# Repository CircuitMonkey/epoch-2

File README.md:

# epoch-2
Epoch Vibrator Controller *(Haptic Field Emitter)* 2 - Now with 100% more edge...

## Description
A follow on to [Epoch 1](https://github.com/CircuitMonkey/epoch).  Designed in 2025. Replaced by [Epoch 3](https://github.com/CircuitMonkey/epoch-3) in 2026. Redesigned with [AdaFruit Qualia ESP32](https://www.adafruit.com/product/5800) and a [Amazon 4-inch IPS (GT911 touch)](https://www.amazon.com/dp/B0D9H3HWR3).  Motors driven with [pca9685 PWM controller](https://learn.adafruit.com/adafruit-16-channel-pwm-servo-hat-for-raspberry-pi)/[Amazon PCA9685 Board](https://www.amazon.com/dp/B0D73811V8) and FET outputs in order to drive bigger motors.  Epoch 1 was limited to 120mA maximum motor drive (because of PWM controller choice) and some larger "rumble" motors need 180mA or higher.

## Features
 - [Adafruit Qualia ESP32-S3 RGB666](https://www.adafruit.com/product/5800)
 - [Amazon 4-inch IPS (GT911 touch)](https://www.amazon.com/dp/B0D9H3HWR3)
 - [pca9685 PWM controller](https://learn.adafruit.com/adafruit-16-channel-pwm-servo-hat-for-raspberry-pi)
 - [LiPo Battery - 62mm x 50mm, 2500mAH, Adafruit](https://www.adafruit.com/product/328)
 - TRS 3.5mm type cables (two motors per connector)
 - FET outputs in order to drive bigger motors.
 - Used [Electric Mini Micro Vibration Motor DC 1.5V/3V/6V 1000RPM M20 with Brass Eccentric Rotating Wheel ](https://www.amazon.com/dp/B07X7MKKQH) in attachments.
 - Programmed in CircuitPython.

## Dev Notes
 - Hardware was intended to output all 16 channels as two rows of connectors, but only built one row.
 - IPS type display used most of the ESP32 pins.
 - Circuit Python with the IPS display was excrucatingly slow.
 - Touch response time was very slow with Circuit Python and made on-screen sliders frustrating to use.
 - TRS Audio type connectors were a big improvement over Molex MinifitJr type connectors.
 - This platform performed well for almost a year, before Epoch-3 developed.
 - Experimental air pressure input showed promise but was fussy in setup/use and not worth using long term.
 - PCA9685 PWM driver was much easier to code with over older Epoch-1 PWM driver.
 - FET outputs allowed use of slightly bigger motors with more rumble yet allowed for a lower motor speeds for subtle haptic sensations.
 - Custom molds were 3D printed for attachments where silicone was poured over a TPU flex frame that held the motors.
 - Attachments had LEDs built in to indicate intensity of each motor.
 - This design and motor patterns have changed my life, able to realize two or three hour long usage sessions.
 - I look forward to improving on this design in Epoch 3.

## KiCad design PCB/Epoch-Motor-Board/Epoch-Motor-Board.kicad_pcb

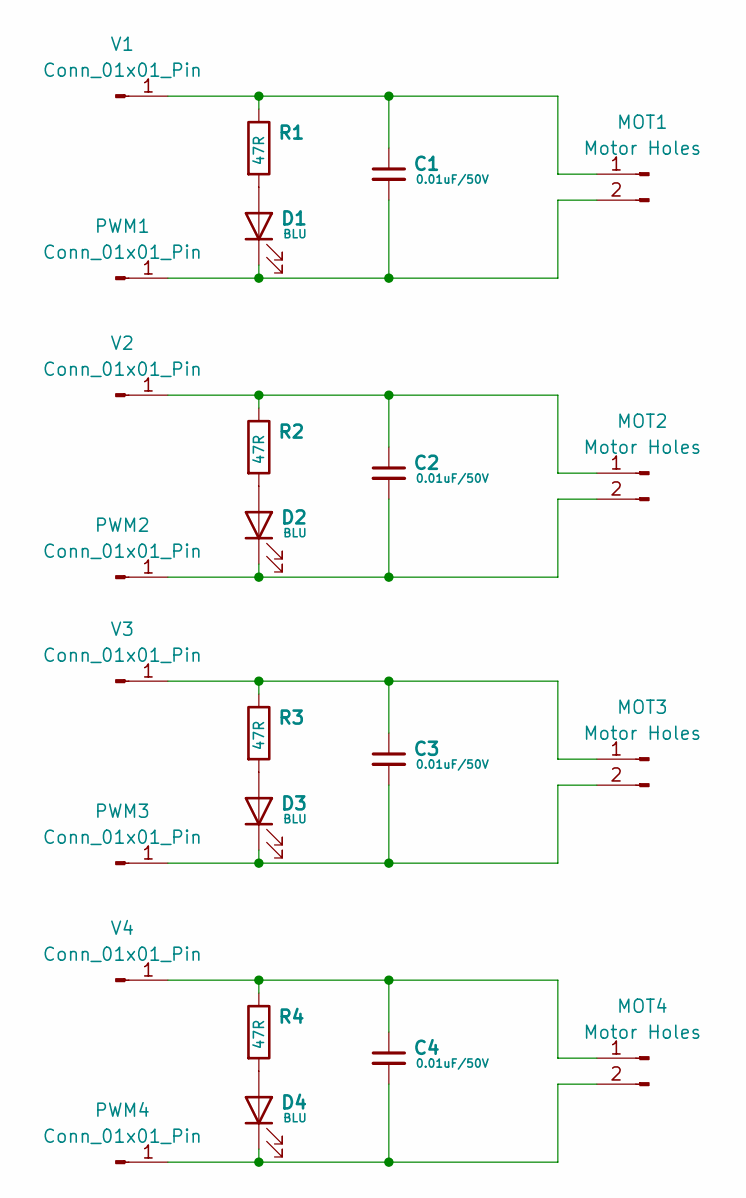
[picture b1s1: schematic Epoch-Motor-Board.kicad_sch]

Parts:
C1, C2, C3, C4: 0.01uF/50V; C_0603_1608Metric
D1, D2, D3, D4: BLU; LED_0603_1608Metric
MOT1, MOT2, MOT3, MOT4: Motor Holes; Motor-PCB
PWM1, PWM2, PWM3, PWM4: Conn_01x01_Pin; TestPoint_Pad_D2.0mm
R1, R2, R3, R4: 47R; R_0603_1608Metric
V1, V2, V3, V4: Conn_01x01_Pin; TestPoint_Pad_2.0x2.0mm

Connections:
unnamed: D1.2 (A), R1.2
unnamed: C1.2, D1.1 (K), MOT1.2, PWM1.1
unnamed: D2.2 (A), R2.2
unnamed: C2.2, D2.1 (K), MOT2.2, PWM2.1
unnamed: D3.2 (A), R3.2
unnamed: C3.2, D3.1 (K), MOT3.2, PWM3.1
unnamed: D4.2 (A), R4.2
unnamed: C4.2, D4.1 (K), MOT4.2, PWM4.1
unnamed: C1.1, MOT1.1, R1.1, V1.1
unnamed: C2.1, MOT2.1, R2.1, V2.1
unnamed: C3.1, MOT3.1, R3.1, V3.1
unnamed: C4.1, MOT4.1, R4.1, V4.1

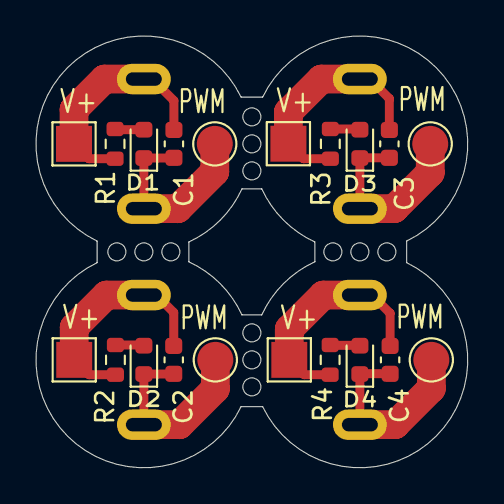
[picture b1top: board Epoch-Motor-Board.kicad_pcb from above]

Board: 2 copper layers, 24.0 x 24.0 mm, 24 parts (0 on the bottom side), 12 nets.

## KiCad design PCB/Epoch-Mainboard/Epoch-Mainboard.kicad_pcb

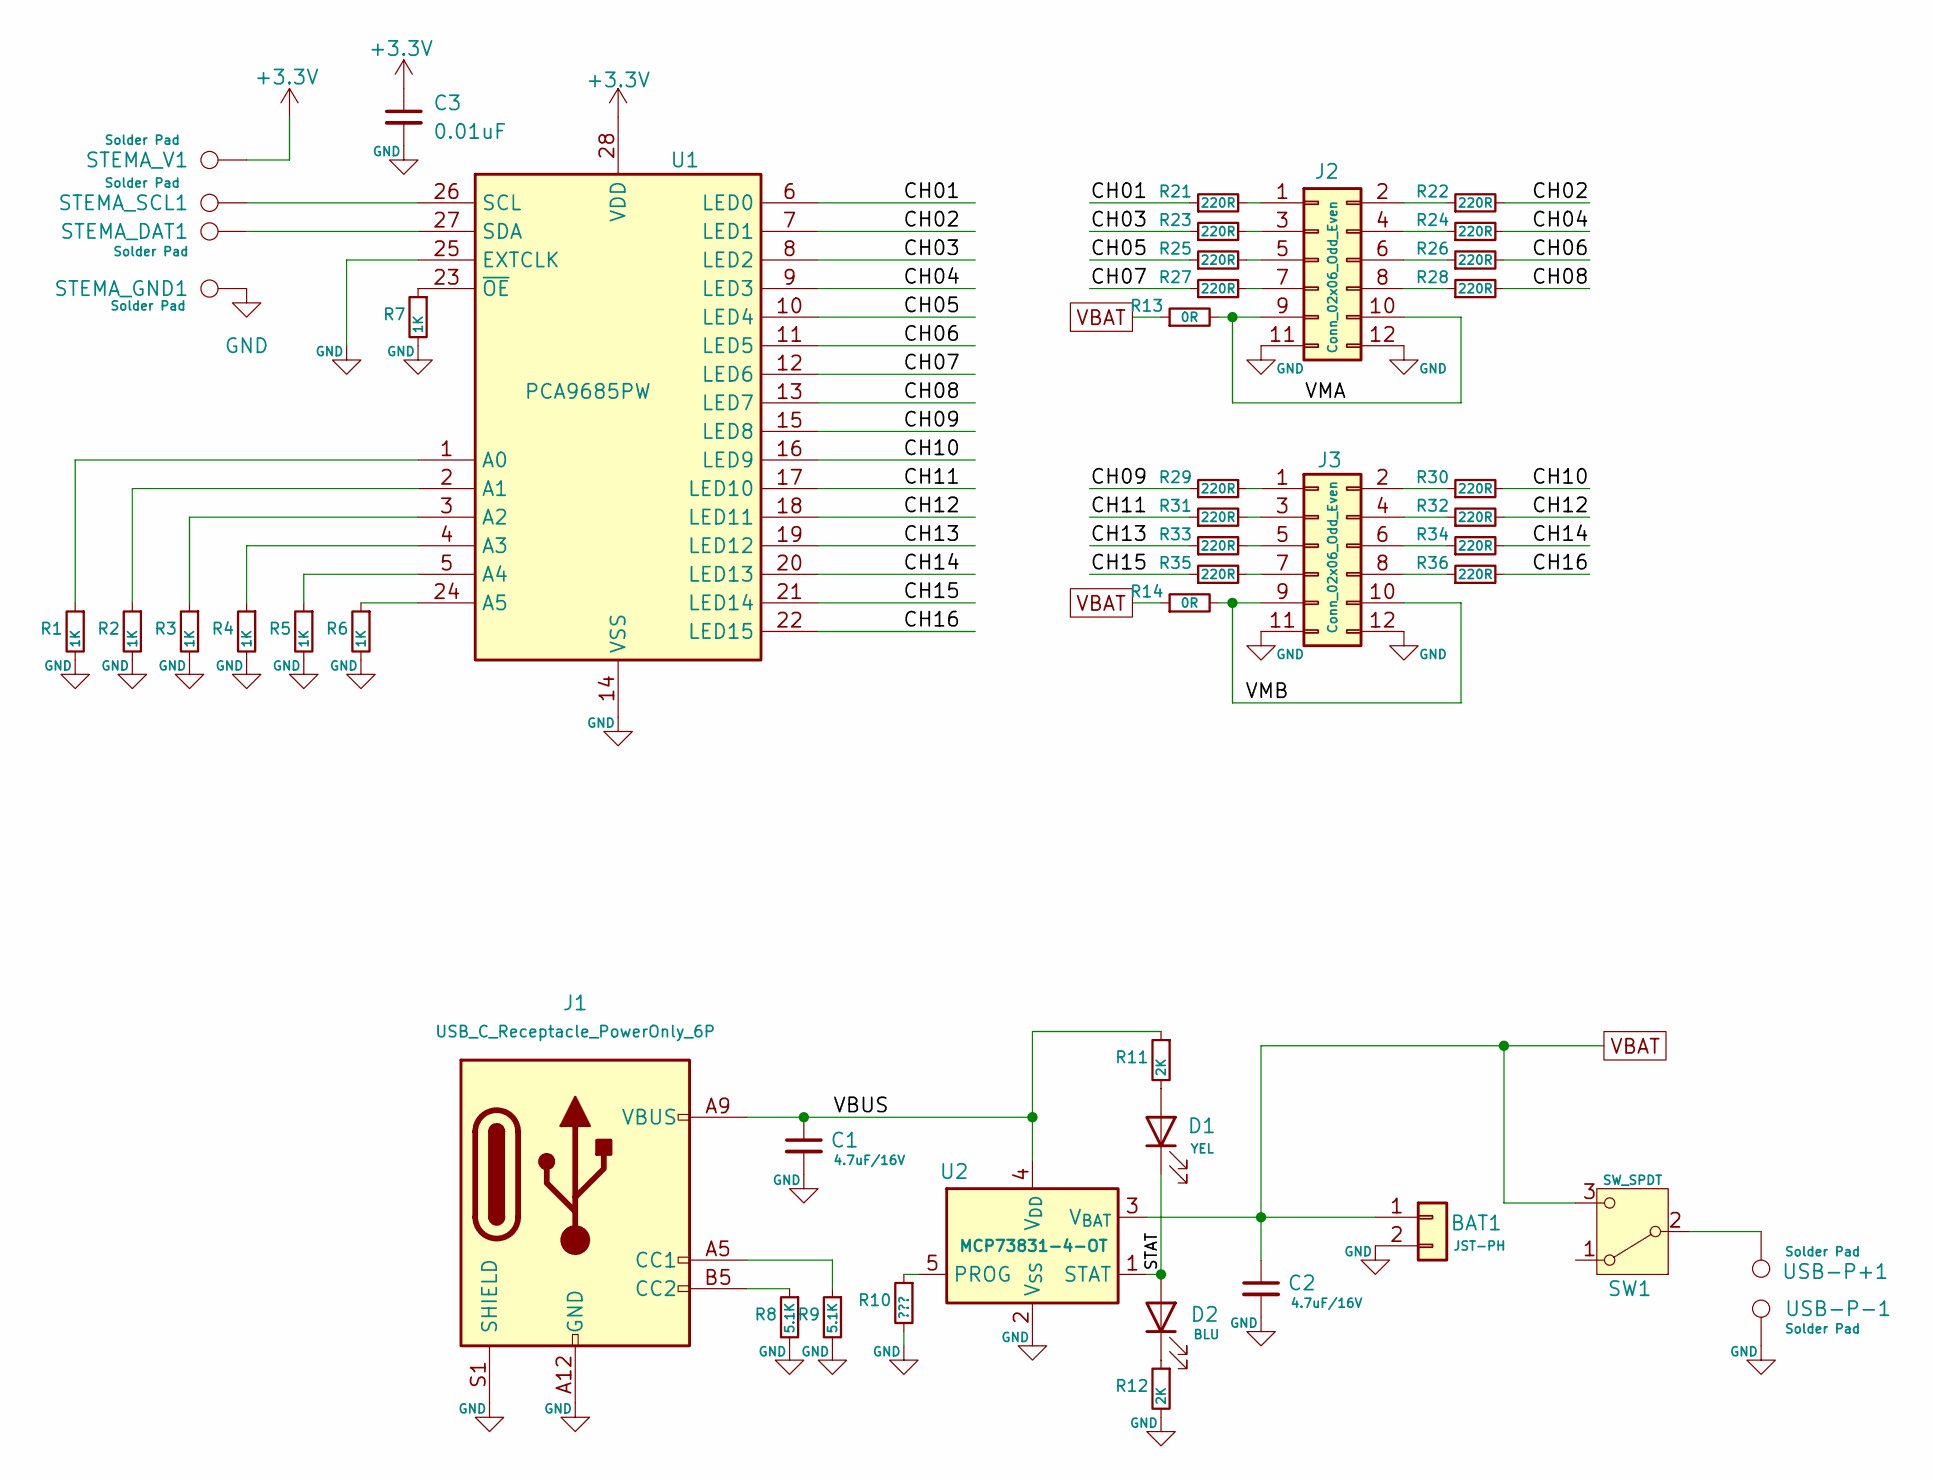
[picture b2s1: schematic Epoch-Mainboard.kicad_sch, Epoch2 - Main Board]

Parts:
BAT1: JST-PH; JST_PH_S2B-PH-K_1x02_P2.00mm_Horizontal
C1, C2: 4.7uF/16V; C_0603_1608Metric
C3: 0.01uF; C_0603_1608Metric
D1: YEL; LED_0603_1608Metric
D2: BLU; LED_0603_1608Metric
J1: USB_C_Receptacle_PowerOnly_6P; USB_C_Receptacle_HRO_TYPE-C-31-M-17
J2, J3: Conn_02x06_Odd_Even; PinHeader_2x06_P2.54mm_Vertical
R1, R2, R3, R4, R5, R6, R7: 1K; R_0603_1608Metric
R8, R9: 5.1K; R_0603_1608Metric
R10: ???; R_0603_1608Metric
R11, R12: 2K; R_0603_1608Metric
R13, R14: 0R; R_1206_3216Metric
R21, R22, R23, R24, R25, R26, R27, R28, R29, R30, R31, R32, R33, R34, R35, R36: 220R; R_0603_1608Metric
STEMA_DAT1: Solder Pad; TestPoint_Pad_D2.0mm
STEMA_GND1: Solder Pad; TestPoint_Pad_D2.0mm
STEMA_SCL1: Solder Pad; TestPoint_Pad_D2.0mm
STEMA_V1: Solder Pad; TestPoint_Pad_D2.0mm
SW1: SW_SPDT; SW_Slide_SPDT_Angled_CK_OS102011MA1Q
U1: PCA9685PW; TSSOP-28_4.4x9.7mm_P0.65mm
U2: MCP73831-4-OT; SOT-23-5
USB-P+1: Solder Pad; TestPoint_Pad_D2.0mm
USB-P-1: Solder Pad; TestPoint_Pad_D2.0mm

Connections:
+3.3V: C3.1, STEMA_V1.1, U1.28 (VDD)
/CH01: R21.1, U1.6 (LED0)
/CH02: R22.2, U1.7 (LED1)
/CH03: R23.1, U1.8 (LED2)
/CH04: R24.2, U1.9 (LED3)
/CH05: R25.1, U1.10 (LED4)
/CH06: R26.2, U1.11 (LED5)
/CH07: R27.1, U1.12 (LED6)
/CH08: R28.2, U1.13 (LED7)
/CH09: R29.1, U1.15 (LED8)
/CH10: R30.2, U1.16 (LED9)
/CH11: R31.1, U1.17 (LED10)
/CH12: R32.2, U1.18 (LED11)
/CH13: R33.1, U1.19 (LED12)
/CH14: R34.2, U1.20 (LED13)
/CH15: R35.1, U1.21 (LED14)
/CH16: R36.2, U1.22 (LED15)
/STAT: D1.1 (K), D2.2 (A), U2.1 (STAT)
/VBUS: C1.1, J1.A9 (VBUS), J1.B9 (VBUS), R11.1, U2.4 (V_{DD})
/VMA: J2.9, J2.10, R13.2
/VMB: J3.9, J3.10, R14.2
GND: BAT1.2, C1.2, C2.2, C3.2, J1.A12 (GND), J1.B12 (GND), J1.S1 (SHIELD), J2.11, J2.12, J3.11, J3.12, R1.2, R2.2, R3.2, R4.2, R5.2, R6.2, R7.2, R8.2, R9.2, R10.2, R12.2, STEMA_GND1.1, U1.14 (VSS), U1.25 (EXTCLK), U2.2 (V_{SS}), USB-P-1.1
unnamed: D1.2 (A), R11.2
unnamed: D2.1 (K), R12.1
unnamed: J1.A5 (CC1), R9.1
unnamed: J1.B5 (CC2), R8.1
unnamed: J2.1, R21.2
unnamed: J2.2, R22.1
unnamed: J2.3, R23.2
unnamed: J2.4, R24.1
unnamed: J2.5, R25.2
unnamed: J2.6, R26.1
unnamed: J2.7, R27.2
unnamed: J2.8, R28.1
unnamed: J3.1, R29.2
unnamed: J3.2, R30.1
unnamed: J3.3, R31.2
unnamed: J3.4, R32.1
unnamed: J3.5, R33.2
unnamed: J3.6, R34.1
unnamed: J3.7, R35.2
unnamed: J3.8, R36.1
unnamed: SW1.2 (B), USB-P+1.1
unnamed: R1.1, U1.1 (A0)
unnamed: R2.1, U1.2 (A1)
unnamed: R3.1, U1.3 (A2)
unnamed: R4.1, U1.4 (A3)
unnamed: R5.1, U1.5 (A4)
unnamed: R6.1, U1.24 (A5)
unnamed: STEMA_SCL1.1, U1.26 (SCL)
unnamed: STEMA_DAT1.1, U1.27 (SDA)
unnamed: R7.1, U1.23 (~OE)
unnamed: R10.1, U2.5 (PROG)
VBAT: BAT1.1, C2.1, R13.1, R14.1, SW1.3 (C), U2.3 (V_{BAT})

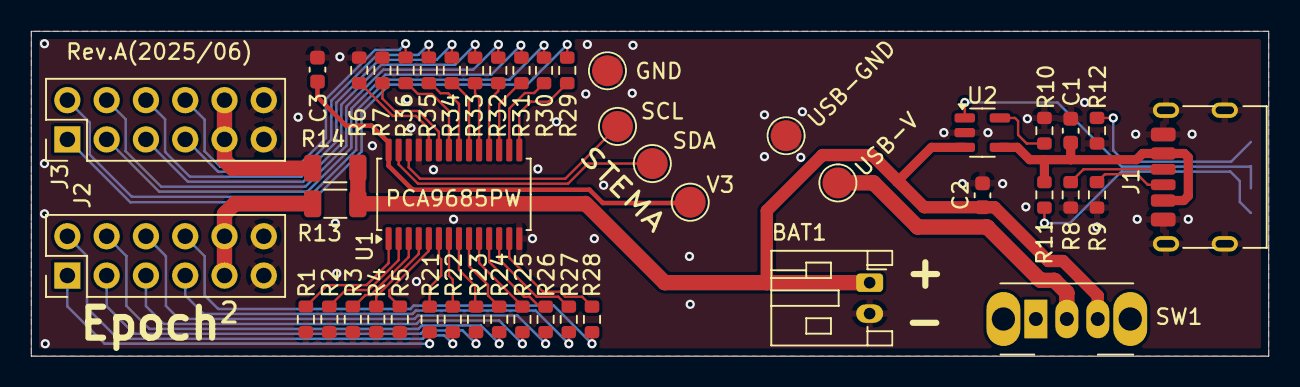
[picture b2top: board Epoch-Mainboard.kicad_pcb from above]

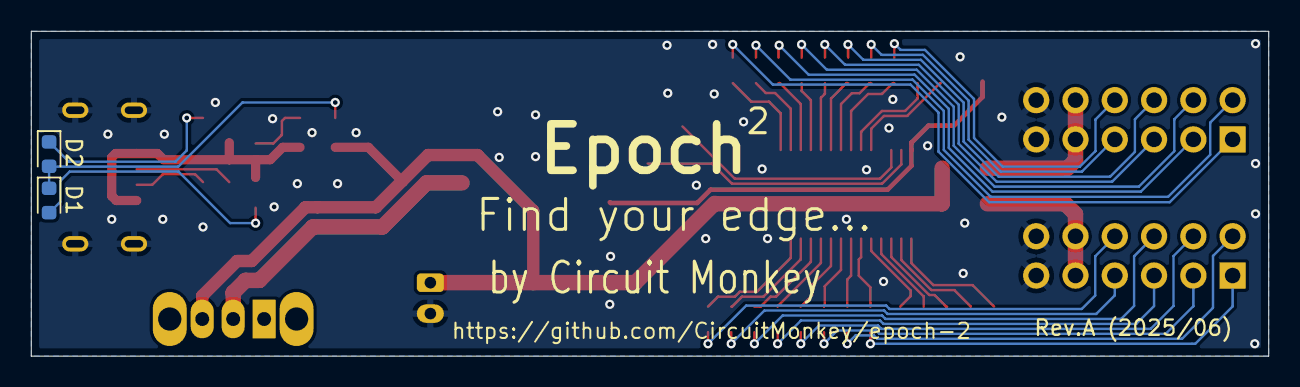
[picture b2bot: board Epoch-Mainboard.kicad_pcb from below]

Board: 2 copper layers, 80.0 x 21.0 mm, 48 parts (2 on the bottom side), 54 nets.

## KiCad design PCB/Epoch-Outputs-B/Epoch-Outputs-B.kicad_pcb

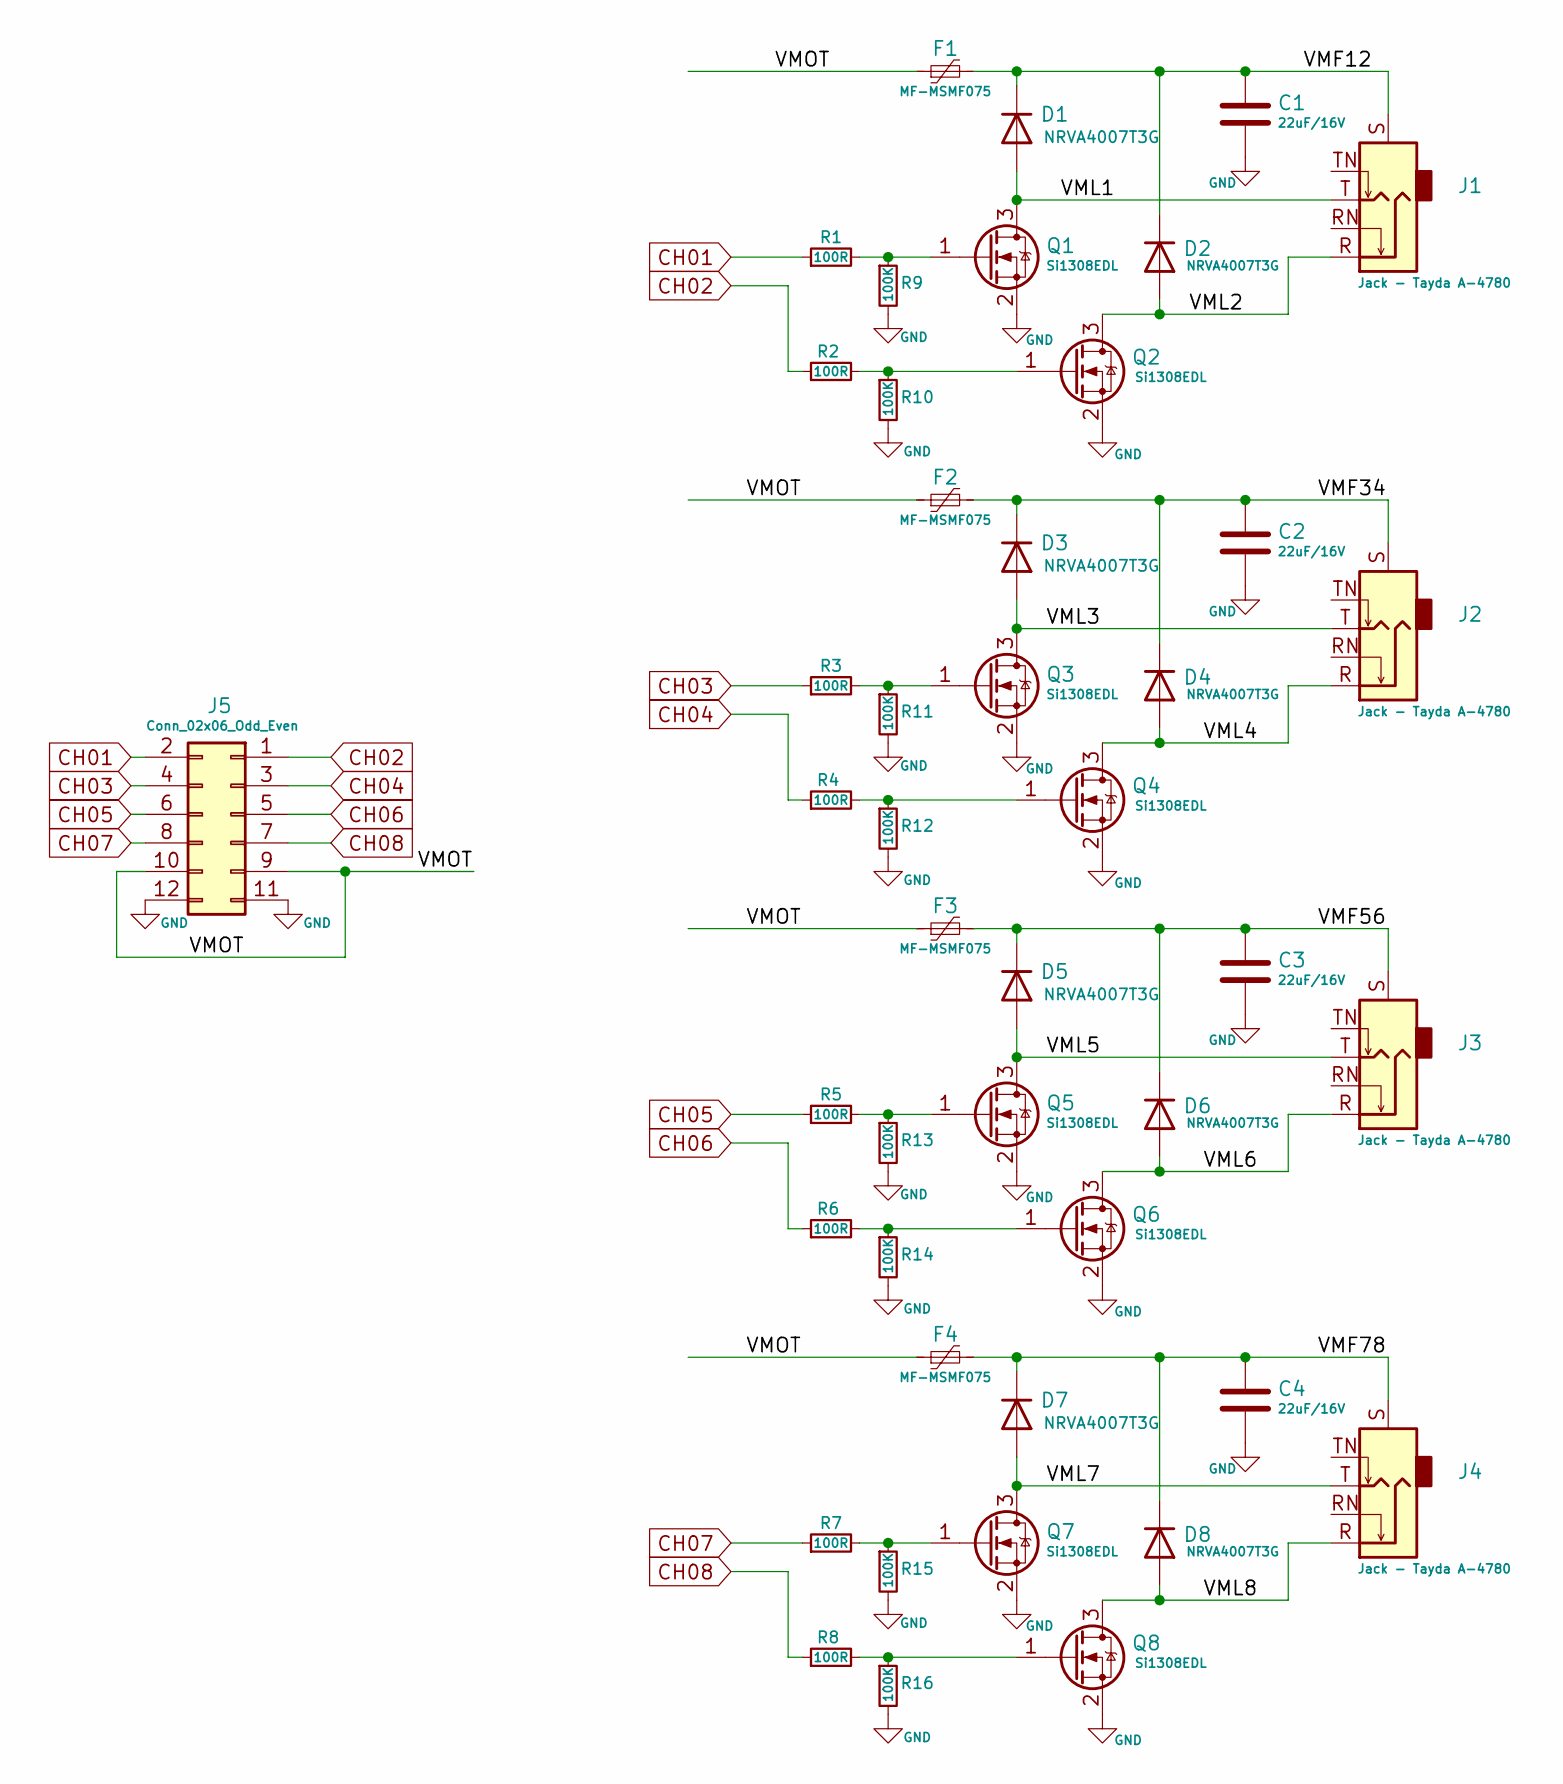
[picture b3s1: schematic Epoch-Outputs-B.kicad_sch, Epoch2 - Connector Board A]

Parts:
C1, C2, C3, C4: 22uF/16V; C_1812_4532Metric
D1, D2, D3, D4, D5, D6, D7, D8: NRVA4007T3G; D_SMA
F1, F2, F3, F4: MF-MSMF075; R_1812_4532Metric
J1, J2, J3, J4: Jack - Tayda A-4780; Jack_3.5mm_CUI_SJ1-3515N_Horizontal
J5: Conn_02x06_Odd_Even; PinHeader_2x06_P2.54mm_Vertical
Q1, Q2, Q3, Q4, Q5, Q6, Q7, Q8: Si1308EDL; SOT-323_SC-70
R1, R2, R3, R4, R5, R6, R7, R8: 100R; R_0603_1608Metric
R9, R10, R11, R12, R13, R14, R15, R16: 100K; R_0603_1608Metric

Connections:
/VMF12: C1.1, D1.1 (K), D2.1 (K), F1.2, J1.S
/VMF34: C2.1, D3.1 (K), D4.1 (K), F2.2, J2.S
/VMF56: C3.1, D5.1 (K), D6.1 (K), F3.2, J3.S
/VMF78: C4.1, D7.1 (K), D8.1 (K), F4.2, J4.S
/VML1: D1.2 (A), J1.T, Q1.3 (D)
/VML2: D2.2 (A), J1.R, Q2.3 (D)
/VML3: D3.2 (A), J2.T, Q3.3 (D)
/VML4: D4.2 (A), J2.R, Q4.3 (D)
/VML5: D5.2 (A), J3.T, Q5.3 (D)
/VML6: D6.2 (A), J3.R, Q6.3 (D)
/VML7: D7.2 (A), J4.T, Q7.3 (D)
/VML8: D8.2 (A), J4.R, Q8.3 (D)
/VMOT: F1.1, F2.1, F3.1, F4.1, J5.9, J5.10
CH01: J5.2, R1.1
CH02: J5.1, R2.1
CH03: J5.4, R3.1
CH04: J5.3, R4.1
CH05: J5.6, R5.1
CH06: J5.5, R6.1
CH07: J5.8, R7.1
CH08: J5.7, R8.1
GND: C1.2, C2.2, C3.2, C4.2, J5.11, J5.12, Q1.2 (S), Q2.2 (S), Q3.2 (S), Q4.2 (S), Q5.2 (S), Q6.2 (S), Q7.2 (S), Q8.2 (S), R9.2, R10.2, R11.2, R12.2, R13.2, R14.2, R15.2, R16.2
unnamed: Q1.1 (G), R1.2, R9.1
unnamed: Q2.1 (G), R2.2, R10.1
unnamed: Q3.1 (G), R3.2, R11.1
unnamed: Q4.1 (G), R4.2, R12.1
unnamed: Q5.1 (G), R5.2, R13.1
unnamed: Q6.1 (G), R6.2, R14.1
unnamed: Q7.1 (G), R7.2, R15.1
unnamed: Q8.1 (G), R8.2, R16.1

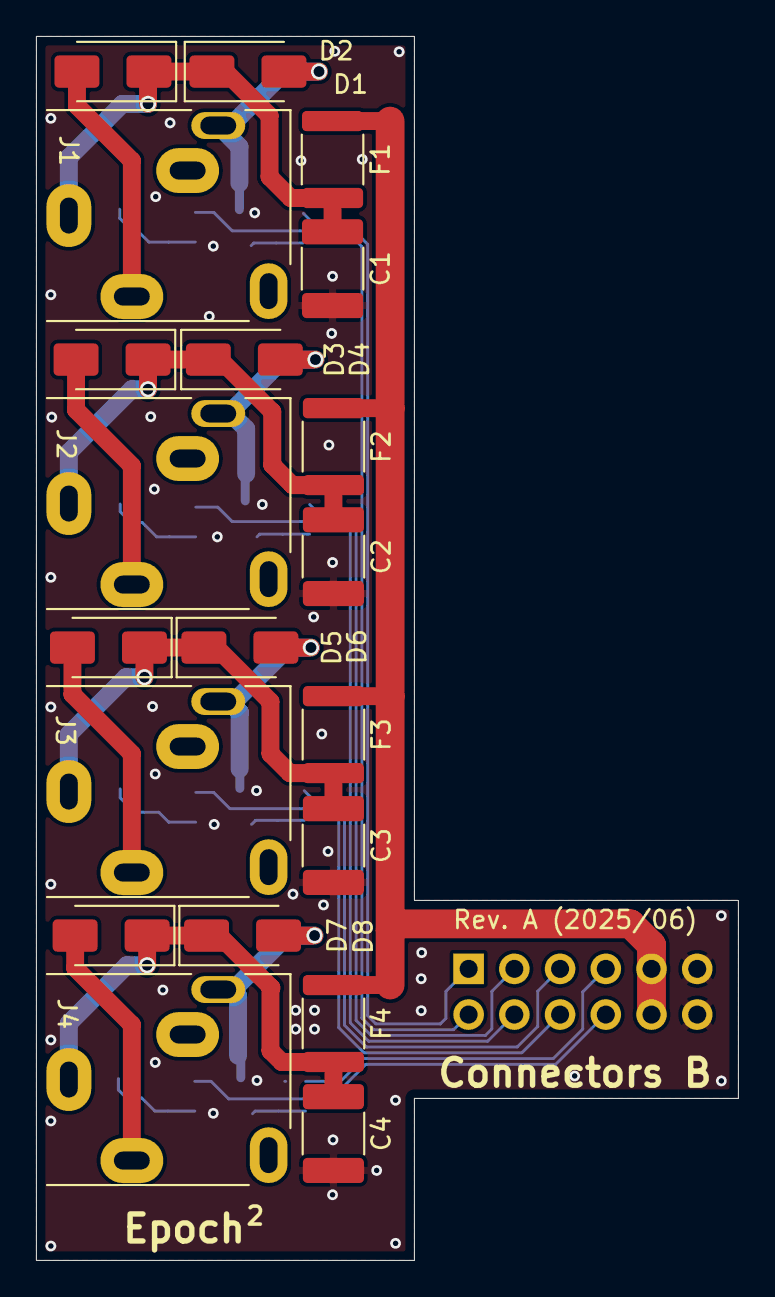
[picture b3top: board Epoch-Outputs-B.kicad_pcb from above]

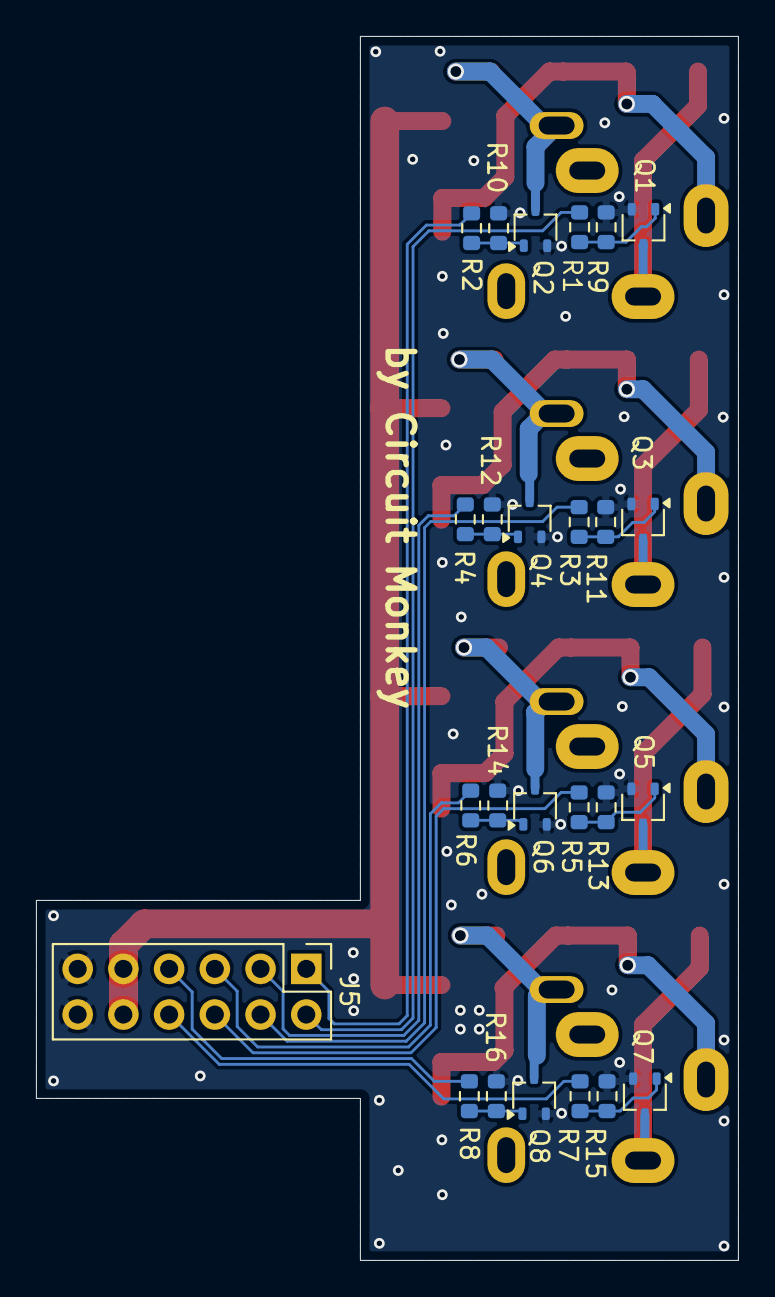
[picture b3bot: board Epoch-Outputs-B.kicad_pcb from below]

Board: 2 copper layers, 39.0 x 68.0 mm, 45 parts (25 on the bottom side), 30 nets.

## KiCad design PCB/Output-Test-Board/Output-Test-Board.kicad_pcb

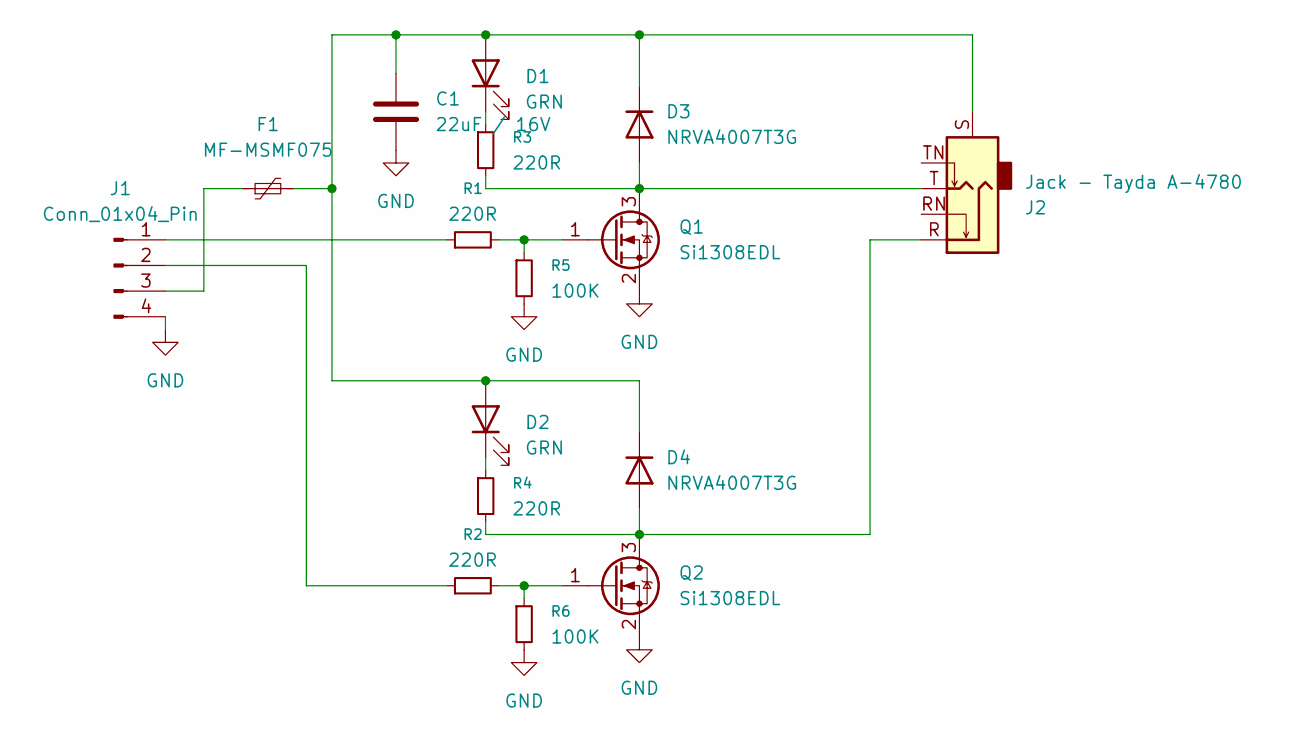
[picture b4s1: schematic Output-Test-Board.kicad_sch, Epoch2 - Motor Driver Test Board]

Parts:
C1: 22uF / 16V; C_1812_4532Metric
D1, D2: GRN; LED_0603_1608Metric
D3, D4: NRVA4007T3G; D_SMA
F1: MF-MSMF075; R_1812_4532Metric
J1: Conn_01x04_Pin; PinHeader_1x04_P2.54mm_Vertical
J2: Jack - Tayda A-4780; Jack_3.5mm_Ledino_KB3SPRS_Horizontal
Q1, Q2: Si1308EDL; SOT-323_SC-70
R1, R2, R3, R4: 220R; R_0603_1608Metric
R5, R6: 100K; R_0603_1608Metric

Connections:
GND: C1.2, J1.4, Q1.2 (S), Q2.2 (S), R5.2, R6.2
unnamed: C1.1, D1.2 (A), D2.2 (A), D3.1 (K), D4.1 (K), F1.2, J2.S
unnamed: D1.1 (K), R3.1
unnamed: D2.1 (K), R4.1
unnamed: D3.2 (A), J2.T, Q1.3 (D), R3.2
unnamed: D4.2 (A), J2.R, Q2.3 (D), R4.2
unnamed: J1.1, R1.1
unnamed: J1.2, R2.1
unnamed: F1.1, J1.3
unnamed: Q1.1 (G), R1.2, R5.1
unnamed: Q2.1 (G), R2.2, R6.1

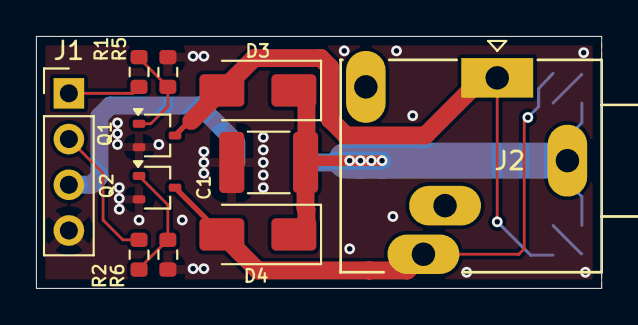
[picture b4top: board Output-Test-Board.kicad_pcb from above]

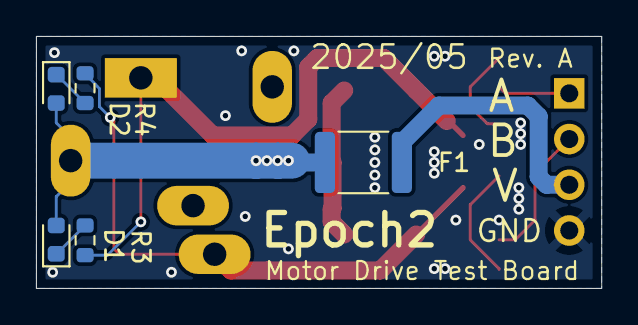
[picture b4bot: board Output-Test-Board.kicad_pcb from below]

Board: 2 copper layers, 31.4 x 14.0 mm, 16 parts (5 on the bottom side), 11 nets.

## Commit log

2025-04-28 Add data sheet for PWM chip.
2025-05-09 Create UI graphics
2025-05-09 First pass of running GUI code.
2025-05-10 Add Channel Settings page
2025-05-10 Add Favorites pages.
2025-05-10 Tune state strings and comments.
2025-05-10 Favorites save/load buttons to those pages work now.
2025-05-10 Remove G-rating for glyphs
2025-05-10 Pass state to Pages. Manual Sliders remember their value.
2025-05-10 Tune configurator and state.
2025-05-14 Motor Test Board - Rev.A
2025-05-14 Add paused state boolean
2025-05-14 Add GUI and Motors update methods.
2025-05-14 Add updateMotors() method
2025-05-14 Tune UI. Add update motors and ui methods.
2025-05-14 Now supports and updates motors and ui.
2025-05-16 Manual mode tracks all 16 sliders. Add cycle sliders.
2025-05-16 Fix issue with motor PWM duty cycle value.
2025-05-16 Various improvements.
2025-05-16 Rework page. Add group selectors.
2025-05-16 Add TODO Note.
2025-05-17 Fix issue with some motors not changing.
2025-05-17 Turn off motors at start of program. Update copyright.
2025-05-19 Track cycle motors value.
2025-05-19 Add motor indicators to Slider.
2025-05-19 Add Motor indicator diamond glyph.
2025-05-19 Get Cycle Page working.
2025-05-19 Cycle page working.
2025-05-20 Tune default sliders for Cycle
2025-05-20 Change default value for a slider to 50 (midpoint)
2025-05-20 Add Speed and Dwell to Cycle mode.
2025-05-21 Add isTouched to ImageButton
2025-05-21 Add epoch button. improve dwell. Use isTouched for button.
2025-05-22 Indicator text now matches arrow value.
2025-05-22 Epoch button fixes.
2025-05-22 Add Pendulum values.
2025-05-22 Add isTouched for TextButton
2025-05-22 Clean up comments
2025-05-22 drag is now Boolean
2025-05-22 Fix slider x position error.
2025-05-22 Move method timing debug code around.
2025-05-22 Support PendulumPage
2025-05-22 Change I2C speed to 400K
2025-05-22 Clean up code.
2025-05-22 Use isTouched method for buttons.
2025-05-22 Support drag as Boolean variable.
2025-05-22 Use isTouched for Buttons.
2025-05-22 Tune Pendulum settings.
2025-05-24 Glyph updates.
2025-05-24 Button updates.
2025-05-24 Buttons take W and H now.
2025-05-24 Convert page into multi mode style.
2025-05-24 Change mode pages.
2025-05-26 Track other mode sliders.
2025-05-26 Move mode select buttons.
2025-05-26 Consoladate modes into one.
2025-05-26 Improvements and fixes.
2025-05-26 Improvements to haptic envelope. Hammer, bug fix.
2025-05-27 Pressure sensor support.
2025-05-27 Sensor support.
2025-05-27 Tune sensor behavior.
2025-06-08 Final PCBs and update gitignore for backups.
2025-06-08 Add STEP models for jack.
2025-06-08 Add BOMs
2025-06-08 Exporting BOM added mysterious "fluff"
2025-06-13 Add Epoch Motor Board.
2025-06-24 Part value changes.
2025-06-30 Fix crash when API changed for ImageButton TextButton.
2025-06-30 Tune soft env. Fix Cyc tick issue. First Use!!!!
2025-09-22 Tune how mode works. Fix motor numbering issue. Add notes.
2025-10-19 Tune cycle motor values.
2026-01-14 Create test file.
2026-01-14 Minor updates.
2026-01-14 STP files for PCBa
2026-02-21 Add images. Update README. Random KiCAD housecleaning.
